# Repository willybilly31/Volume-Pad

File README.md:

# Voluma

Xiao RP2040 based volume/macropad made to make my desk setup easier to use. I was going to make a regular old macropad with just buttons, but i realized that sometimes i would want to change the volume of individual apps on my pc but that can be annoying to do.

## Hardware
- Xiao RP2040
- Addressable RGB LED
- 3 Cherry MX switches
- 3 PTA4543-2015CPB503 slide potentiometers

## Features
- Slide potentiometers for volume controls
- Keyboard Switches for Macros/Shortcuts
- RGB LED

## Screenshots

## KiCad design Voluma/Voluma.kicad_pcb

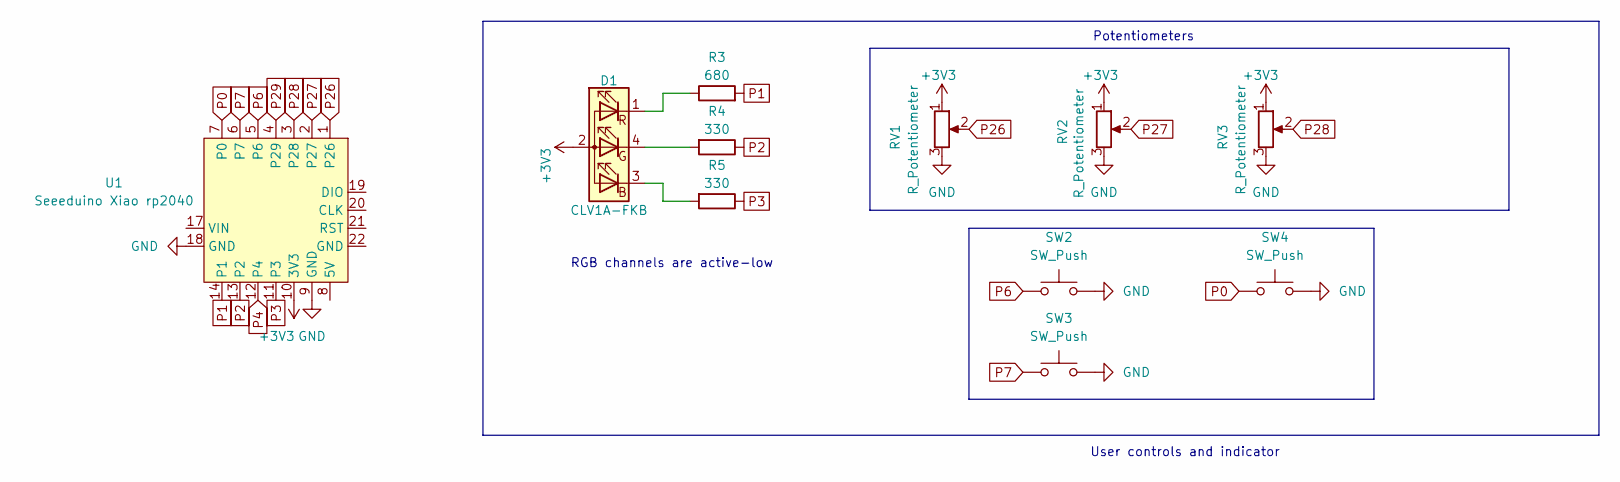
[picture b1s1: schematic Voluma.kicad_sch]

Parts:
D1: CLV1A-FKB; LED_Cree-PLCC4_3.2x2.8mm_CCW
R3: 680; R_0603_1608Metric
R4, R5: 330; R_0603_1608Metric
RV1, RV2, RV3: R_Potentiometer; Potentiometer_Bourns_PTA4543_Single_Slide
SW2, SW3, SW4: SW_Push; SW_Cherry_MX_1.00u_PCB
U1: Seeeduino Xiao rp2040; Xiao_rp2040_ACH

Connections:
+3V3: D1.2 (A), RV1.1, RV2.1, RV3.1, U1.10 (3V3)
GND: RV1.3, RV2.3, RV3.3, SW2.2, SW3.2, SW4.2, U1.9 (GND), U1.18 (GND)
unnamed: D1.3 (BK), R5.2
unnamed: D1.4 (GK), R4.2
unnamed: D1.1 (RK), R3.1
P0: SW4.1, U1.7 (P0)
P1: R3.2, U1.14 (P1)
P2: R4.1, U1.13 (P2)
P3: R5.1, U1.11 (P3)
P4: U1.12 (P4)
P6: SW2.1, U1.5 (P6)
P7: SW3.1, U1.6 (P7)
P26: RV1.2, U1.1 (P26)
P27: RV2.2, U1.2 (P27)
P28: RV3.2, U1.3 (P28)
P29: U1.4 (P29)

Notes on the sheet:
RGB channels are active-low
Potentiometers
User controls and indicator

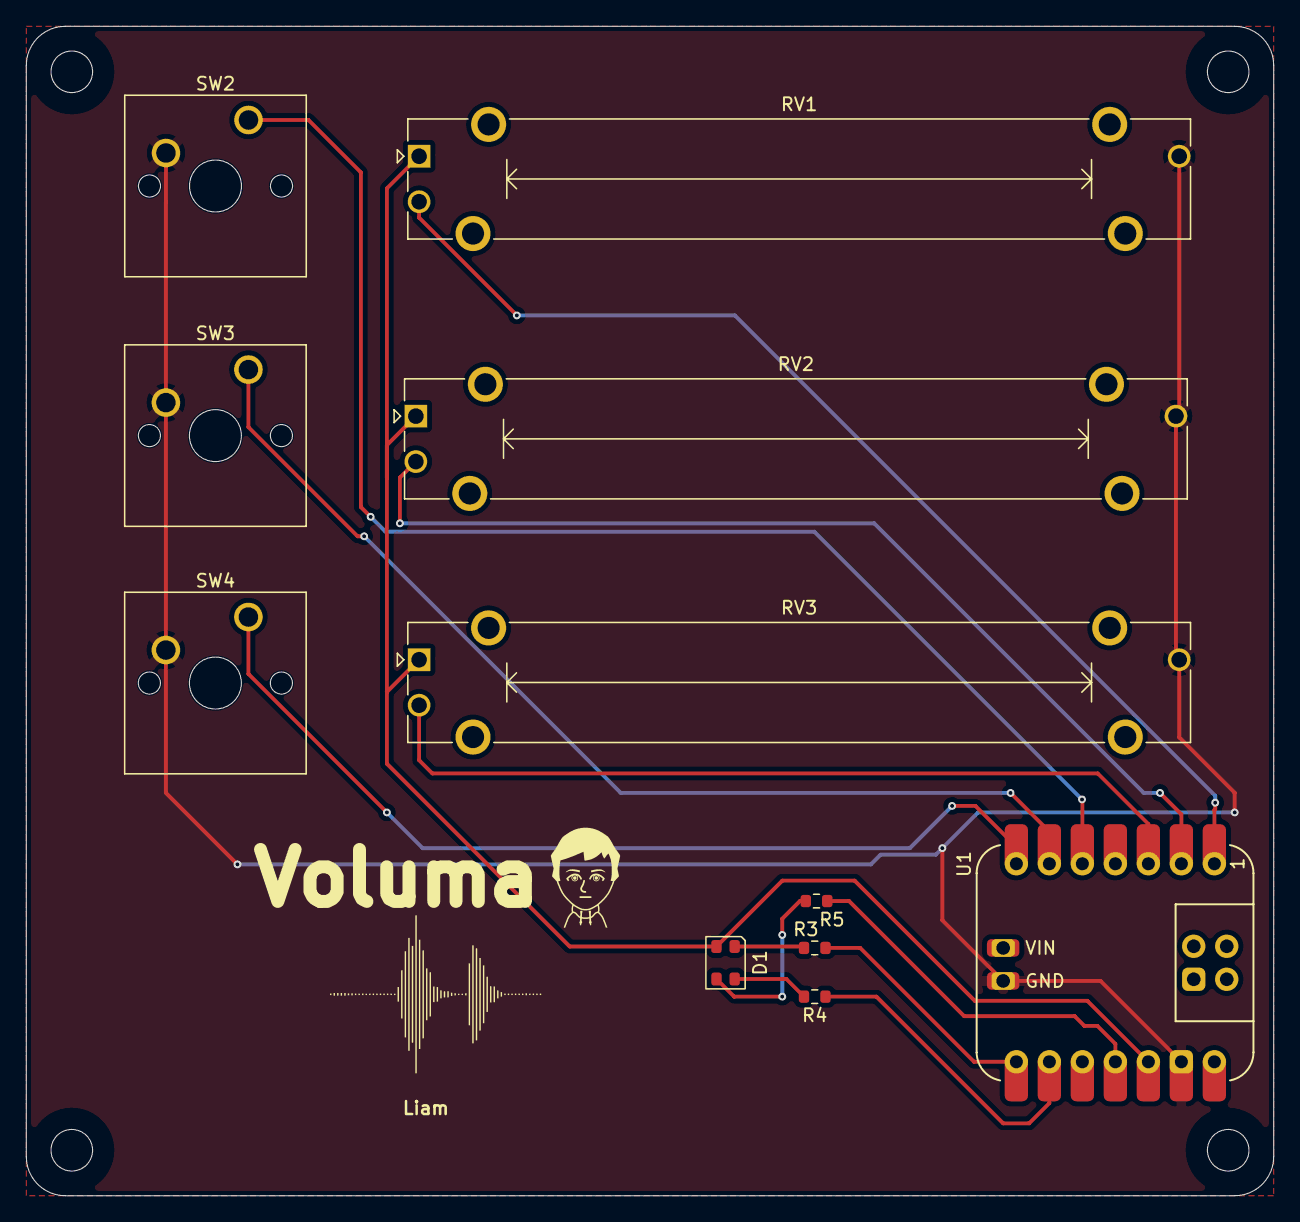
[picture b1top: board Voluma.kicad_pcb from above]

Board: 2 copper layers, 96.0 x 90.0 mm, 15 parts (0 on the bottom side), 14 nets.

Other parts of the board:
H1, H2, H3, H4: MountingHole_3.2mm_M3

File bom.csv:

Designator,Footprint,Quantity,Value,LCSC Part #
D1,LED_Cree-PLCC4_3.2x2.8mm_CCW,1,CLV1A-FKB,
R3,0603,1,680,
"R4, R5",0603,2,330,
"RV1, RV2, RV3",Potentiometer_Bourns_PTA4543_Single_Slide,3,R_Potentiometer,
"SW2, SW3, SW4",SW_Cherry_MX_1.00u_PCB,3,SW_Push,

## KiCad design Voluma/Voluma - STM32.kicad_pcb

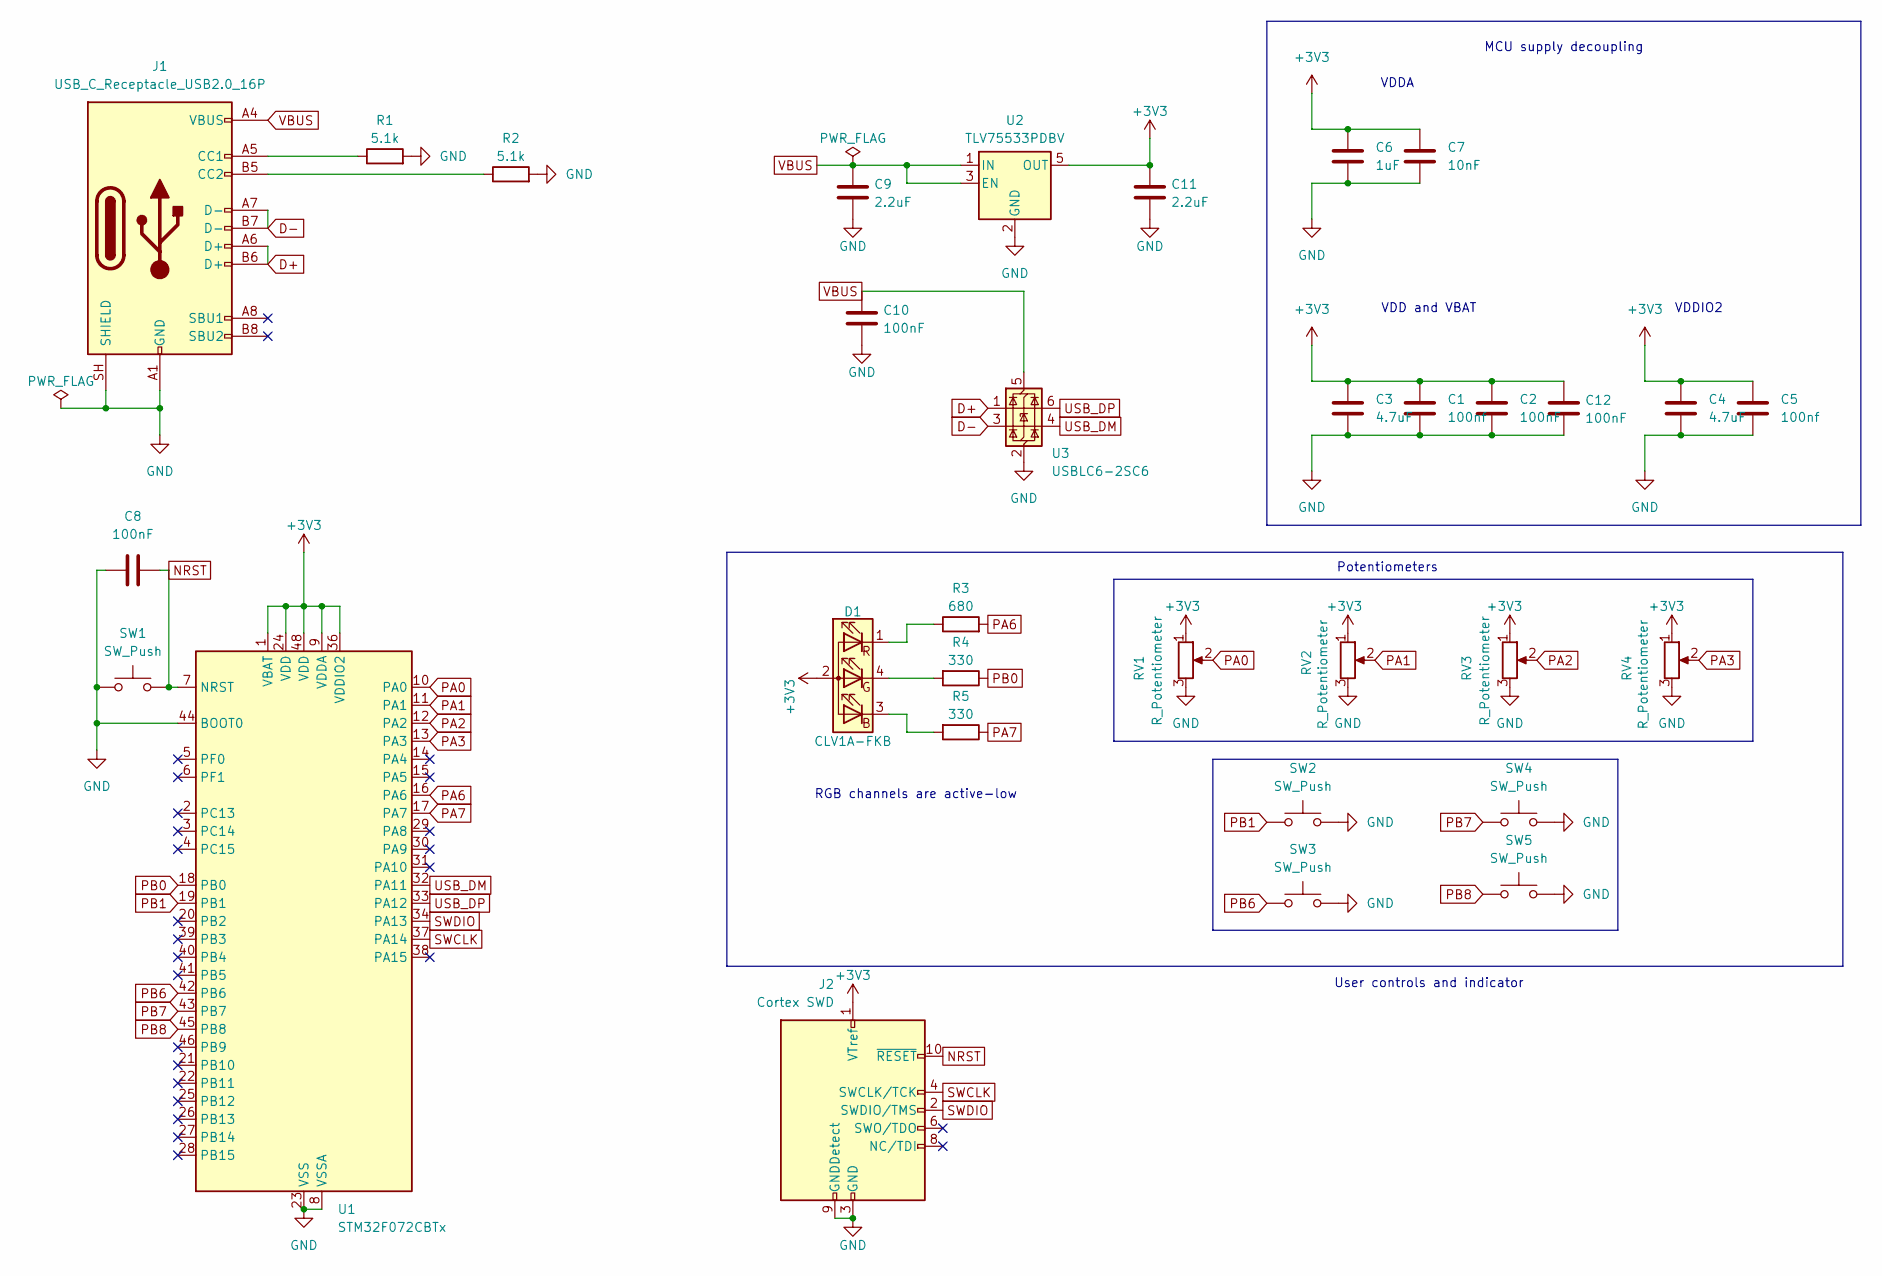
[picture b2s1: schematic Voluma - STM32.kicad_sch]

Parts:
C1, C5: 100nf; C_0603_1608Metric
C2, C8, C10, C12: 100nF; C_0603_1608Metric
C3, C4: 4.7uF; C_0603_1608Metric
C6: 1uF; C_0603_1608Metric
C7: 10nF; C_0603_1608Metric
C9, C11: 2.2uF; C_0603_1608Metric
D1: CLV1A-FKB; LED_Cree-PLCC4_3.2x2.8mm_CCW
J1: USB_C_Receptacle_USB2.0_16P; USB_C_Receptacle_HRO_TYPE-C-31-M-12
J2: Cortex SWD; PinHeader_2x05_P1.27mm_Vertical
R1, R2: 5.1k; R_0603_1608Metric
R3: 680; R_0603_1608Metric
R4, R5: 330; R_0603_1608Metric
RV1, RV2, RV3, RV4: R_Potentiometer; Potentiometer_Bourns_PTA4543_Single_Slide
SW1: SW_Push; SW_SPST_PTS645Sx43SMTR92
SW2, SW3, SW4, SW5: SW_Push; SW_Cherry_MX_1.00u_PCB
U1: STM32F072CBTx; LQFP-48_7x7mm_P0.5mm
U2: TLV75533PDBV; SOT-23-5
U3: USBLC6-2SC6; SOT-23-6

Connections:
+3V3: C1.1, C2.1, C3.1, C4.1, C5.1, C6.1, C7.1, C11.1, C12.1, D1.2 (A), J2.1 (VTref), RV1.1, RV2.1, RV3.1, RV4.1, U1.1 (VBAT), U1.9 (VDDA), U1.24 (VDD), U1.36 (VDDIO2), U1.48 (VDD), U2.5 (OUT)
D+: J1.A6 (D+), J1.B6 (D+), U3.1 (I/O1)
D-: J1.A7 (D-), J1.B7 (D-), U3.3 (I/O2)
GND: C1.2, C2.2, C3.2, C4.2, C5.2, C6.2, C7.2, C8.1, C9.2, C10.2, C11.2, C12.2, J1.A1 (GND), J1.A12 (GND), J1.B1 (GND), J1.B12 (GND), J1.SH (SHIELD), J2.3 (GND), J2.5 (GND), J2.9 (GNDDetect), R1.2, R2.2, RV1.3, RV2.3, RV3.3, RV4.3, SW1.1, SW2.2, SW3.2, SW4.2, SW5.2, U1.8 (VSSA), U1.23 (VSS), U1.35 (VSS), U1.44 (BOOT0), U1.47 (VSS), U2.2 (GND), U3.2 (GND)
NRST: C8.2, J2.10 (~RESET), SW1.2, U1.7 (NRST)
unnamed: D1.3 (BK), R5.2
unnamed: D1.4 (GK), R4.2
unnamed: D1.1 (RK), R3.1
unnamed: J1.A5 (CC1), R1.1
unnamed: J1.B5 (CC2), R2.1
PA0: RV1.2, U1.10 (PA0)
PA1: RV2.2, U1.11 (PA1)
PA2: RV3.2, U1.12 (PA2)
PA3: RV4.2, U1.13 (PA3)
PA6: R3.2, U1.16 (PA6)
PA7: R5.1, U1.17 (PA7)
PB0: R4.1, U1.18 (PB0)
PB1: SW2.1, U1.19 (PB1)
PB6: SW3.1, U1.42 (PB6)
PB7: SW4.1, U1.43 (PB7)
PB8: SW5.1, U1.45 (PB8)
SWCLK: J2.4 (SWCLK/TCK), U1.37 (PA14)
SWDIO: J2.2 (SWDIO/TMS), U1.34 (PA13)
USB_DM: U1.32 (PA11), U3.4 (I/O2)
USB_DP: U1.33 (PA12), U3.6 (I/O1)
VBUS: C9.1, C10.1, J1.A4 (VBUS), J1.A9 (VBUS), J1.B4 (VBUS), J1.B9 (VBUS), U2.1 (IN), U2.3 (EN), U3.5 (VBUS)

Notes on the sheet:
VDD and VBAT
VDDA
VDDIO2
RGB channels are active-low
Potentiometers
MCU supply decoupling
User controls and indicator

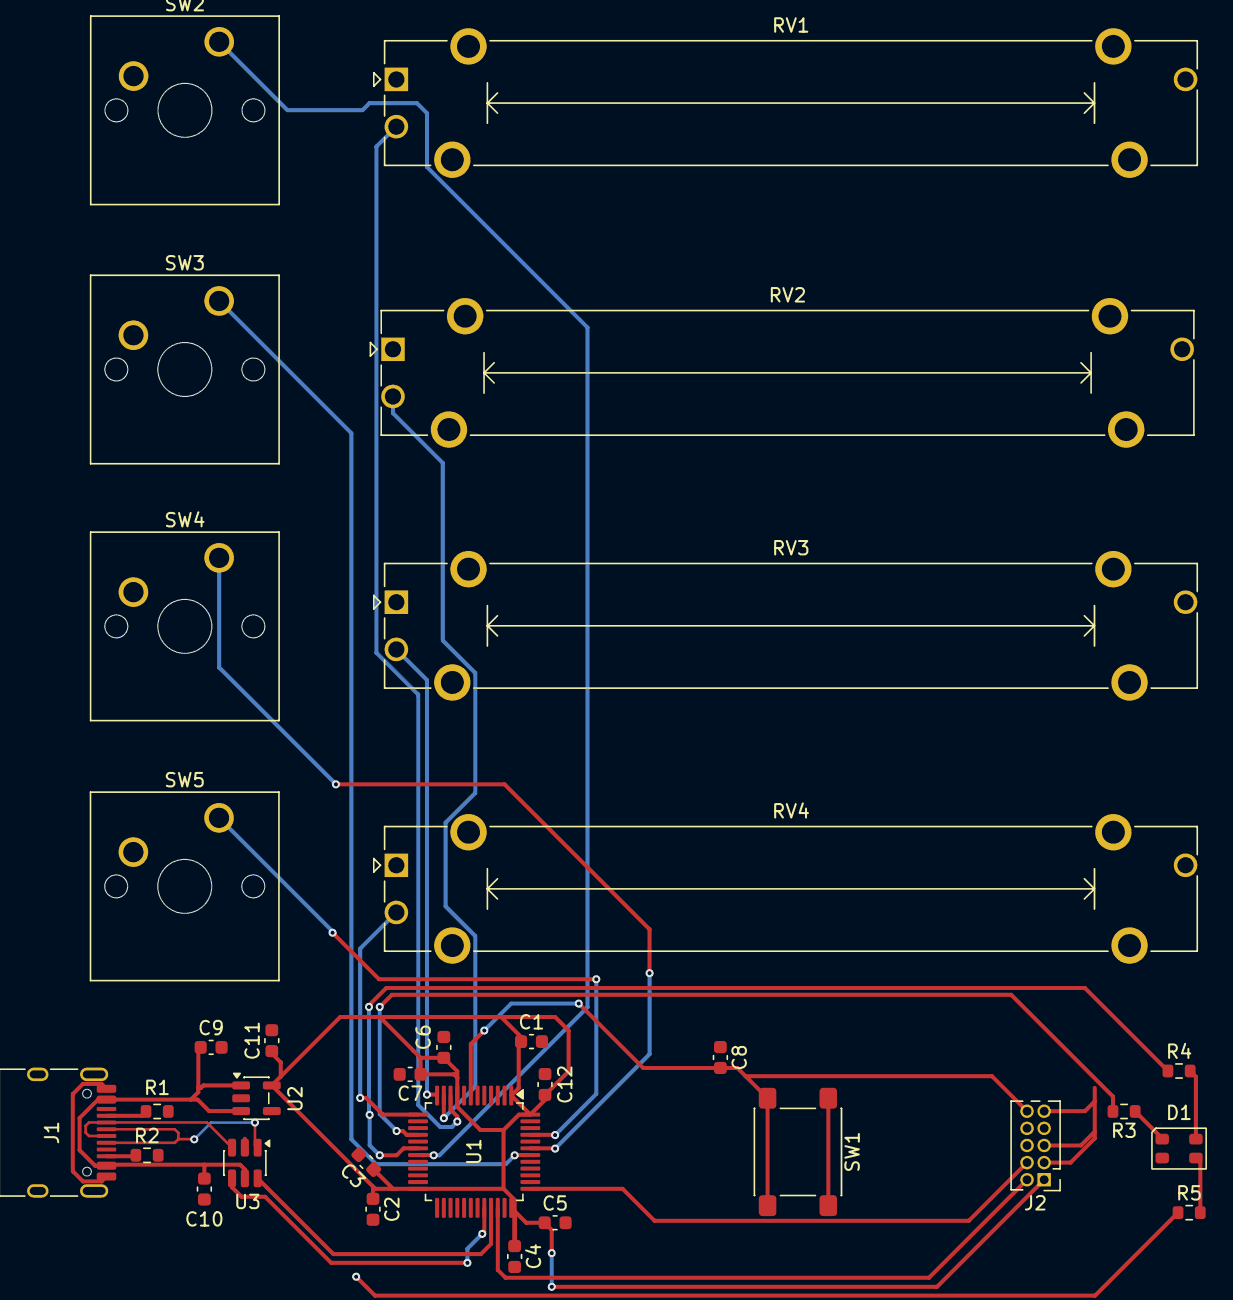
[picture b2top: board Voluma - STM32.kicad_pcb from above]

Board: 2 copper layers, 32 parts (0 on the bottom side), 26 nets.
